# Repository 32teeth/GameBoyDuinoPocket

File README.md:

gameboyDuino - Pocket
==================

-------------

# Introduction

**gameboyDuino** is a programmable touch interface that fits the inside dimensions of the **Offical Gameboy Pocket**. 

The hardware is based on AVR microcontrollers and programmed via [AVR Studio](http://www.atmel.ca/microsite/atmel_studio6/) or the [Arduino IDE](http://arduino.cc/en/Main/Software)

**gameboyDuino.** in it's entirety is open source. Including hardware design, software implementation and libraries
***

##Hardware

#### Eagle CAD
All of the PCB design, schema and board layout files where designed in [CadSoft's Eagle Cad PCB](http://www.cadsoftusa.com/eagle-pcb-design-software/product-overview/?language=en) software.

The .sch and .brd files are available in the [master](https://github.com/32teeth/GameBoyDuinoPocket) folder.

|  front | back  |
|---|---|
|   |   |
| capacitive touch d-pad  | atmega328p  |
| capacitive b and a buttons  |  ftdi com port |
| capacitive start select  |  usb interface |
| additional speaker connection  | interface leds  |
| tft break out | icsp programmable port  |
| accurate drill/screw holes | li-po battery connection  |

###BONUS!!!
We also worked on another project which was shoving the Arduino UNO onto a Gameboy Cartridge. It's in the master folder as well. 

***
# Thanks
Should you run into any trouble, or have further questions, feel free to reach out.

* [ 32teeth](https://www.facebook.com/32teeth)
* [ eugeneyevhen](https://twitter.com/eugeneyevhen)
* [ SparkyJr](32teeth.github.io/SparkyJr)
* [ 32teeth](http://ca.linkedin.com/in/32teeth)

***

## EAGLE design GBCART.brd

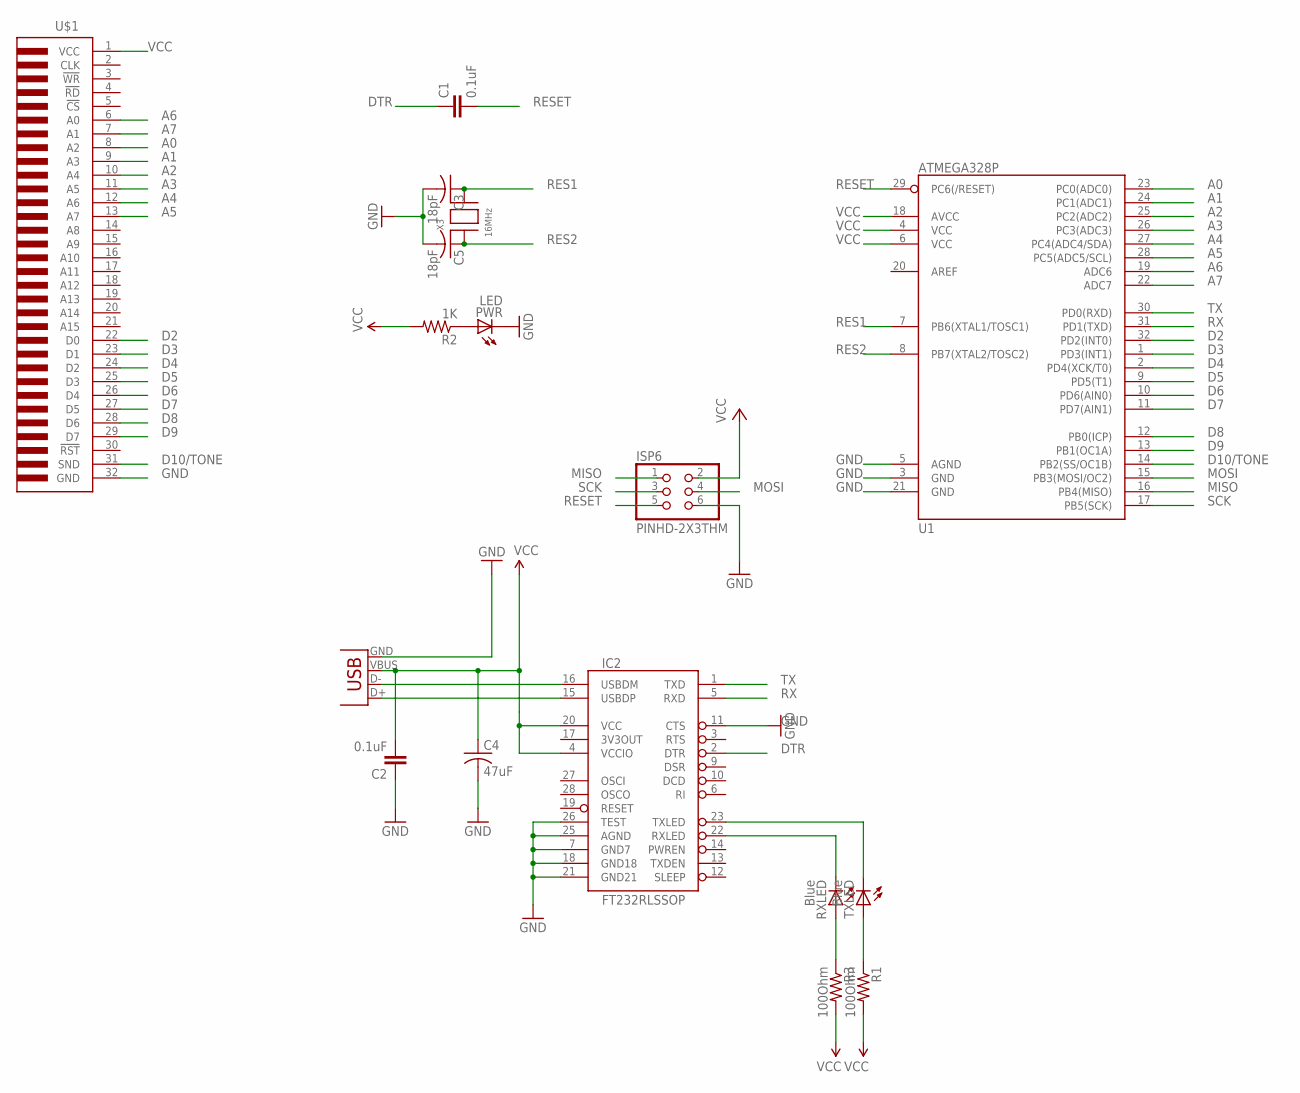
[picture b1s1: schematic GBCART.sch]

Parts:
C1, C2: 0.1uF; 0805
C3, C5: 18pF; C0805K
C4: 47uF; C0805
IC2: FT232RLSSOP; SSOP28DB
ISP6: PINHD-2X3THM; ISP6
PWR: LED; CHIPLED_0805
R1, R3: 100Ohm; R0805
R2: 1K; R0805
RXLED: Blue; CHIPLED_0805
TXLED: Blue; CHIPLED_0805
U1: ATMEGA328P; TQFP32-08
U$1: GBCART-FULL; GBCART
X1: USBSMD; USB-MINIB
X3: 16MHz; NX5032

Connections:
A0: U1.23 (PC0(ADC0)), U$1.8 (A2)
A1: U1.24 (PC1(ADC1)), U$1.9 (A3)
A2: U1.25 (PC2(ADC2)), U$1.10 (A4)
A3: U1.26 (PC3(ADC3)), U$1.11 (A5)
A4: U1.27 (PC4(ADC4/SDA)), U$1.12 (A6)
A5: U1.28 (PC5(ADC5/SCL)), U$1.13 (A7)
A6: U1.19 (ADC6), U$1.6 (A0)
A7: U1.22 (ADC7), U$1.7 (A1)
D2: U1.32 (PD2(INT0)), U$1.22 (D0)
D3: U1.1 (PD3(INT1)), U$1.23 (D1)
D4: U1.2 (PD4(XCK/T0)), U$1.24 (D2)
D5: U1.9 (PD5(T1)), U$1.25 (D3)
D6: U1.10 (PD6(AIN0)), U$1.26 (D4)
D7: U1.11 (PD7(AIN1)), U$1.27 (D5)
D8: U1.12 (PB0(ICP)), U$1.28 (D6)
D9: U1.13 (PB1(OC1A)), U$1.29 (D7)
D10/TONE: U1.14 (PB2(SS/OC1B)), U$1.31 (SND)
D+: IC2.15 (USBDP), X1.D+
D-: IC2.16 (USBDM), X1.D-
DTR: C1.1, IC2.2 (DTR)
GND: C2.1, C3.2, C4.2, C5.2, IC2.7 (GND7), IC2.11 (CTS), IC2.18 (GND18), IC2.21 (GND21), IC2.25 (AGND), IC2.26 (TEST), ISP6.6, PWR.C, U1.3 (GND), U1.5 (AGND), U1.21 (GND), U$1.32 (GND), X1.GND
MISO: ISP6.1, U1.16 (PB4(MISO))
MOSI: ISP6.4, U1.15 (PB3(MOSI/OC2))
unnamed: PWR.A, R2.1
unnamed: R3.1, RXLED.A
unnamed: R1.1, TXLED.A
RES1: C3.1, U1.7 (PB6(XTAL1/TOSC1)), X3.P$2
RES2: C5.1, U1.8 (PB7(XTAL2/TOSC2)), X3.P$1
RESET: C1.2, ISP6.5, U1.29 (PC6(/RESET))
RX: IC2.5 (RXD), U1.31 (PD1(TXD))
RXLED: IC2.22 (RXLED), RXLED.C
SCK: ISP6.3, U1.17 (PB5(SCK))
TX: IC2.1 (TXD), U1.30 (PD0(RXD))
TXLED: IC2.23 (TXLED), TXLED.C
VCC: C2.2, C4.1, IC2.4 (VCCIO), IC2.20 (VCC), ISP6.2, R1.2, R2.2, R3.2, U1.4 (VCC), U1.6 (VCC), U1.18 (AVCC), U$1.1 (VCC), X1.VBUS

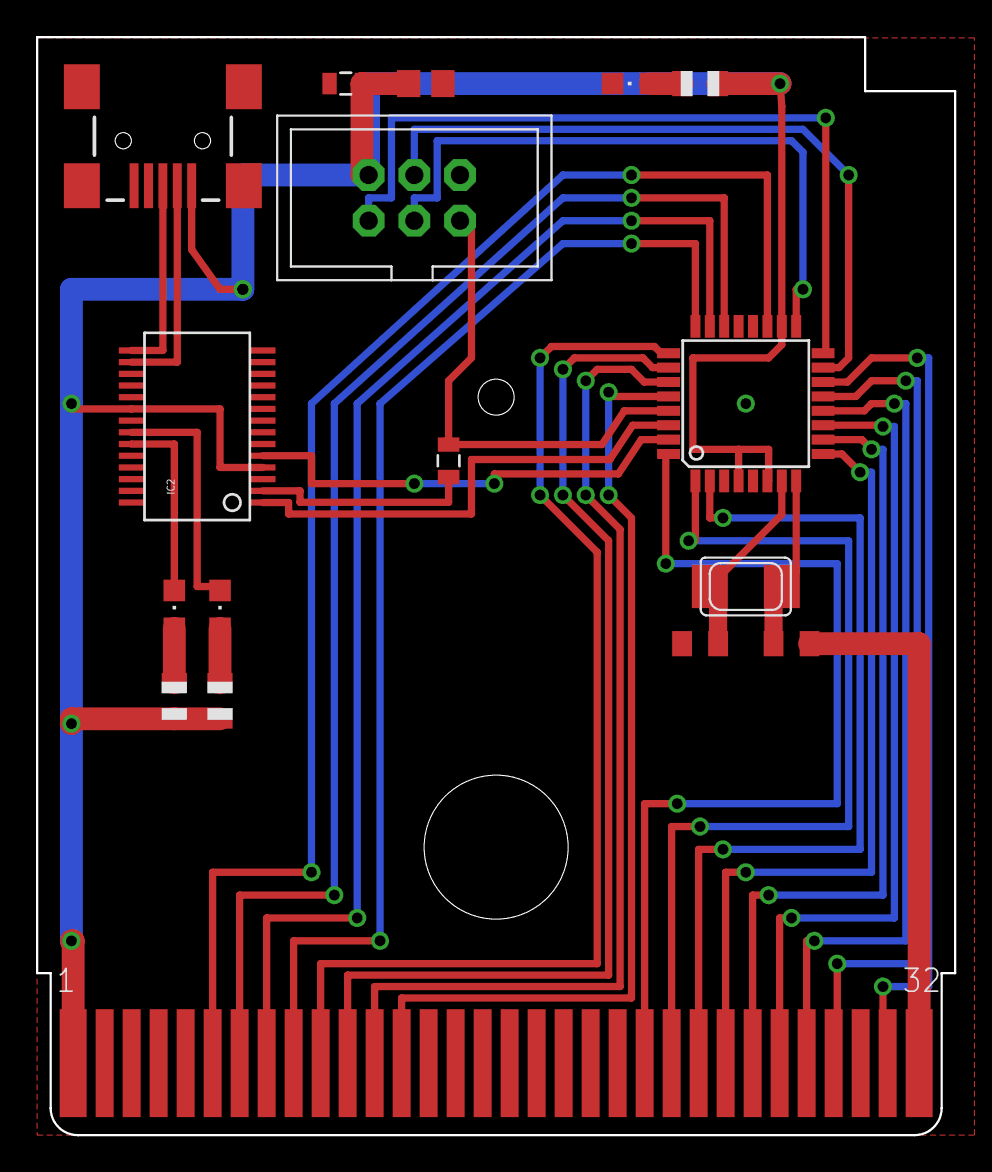
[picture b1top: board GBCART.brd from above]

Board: 2 copper layers, 51.0 x 61.0 mm, 17 parts (0 on the bottom side), 35 nets.

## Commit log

2014-10-05 added read me
2014-10-05 link
2014-10-06 added GBC
